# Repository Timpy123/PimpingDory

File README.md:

# PimpingDory

Two things live here:

1. **Software that talks to a [Chasing Dory](https://www.chasing.com) underwater
   drone without the vendor app** — download the media, watch the live camera,
   read telemetry, work the lights, drive the thrusters. No account, no login,
   no phone.
2. **A log of modifying the hardware** — a light rig, a bigger battery, more
   thrust, more storage, and a home-built metal detector. Some of it built, none
   of it finished, all of it written down.

Everything was worked out from the outside and tested on a real drone.
Not affiliated with or endorsed by Chasing.

## Hardware upgrades

Each one has its own folder with notes, photos and parts.

| upgrade | what | state |
|---|---|---|
| [**Light rig**](LightRig/) | two Wurkkos DL07 lights on an aluminium arm clamped to the hull | contour taken, aluminium strap trial-fitted |
| [**Metal detector**](MetalDetector/) | a self-contained pulse-induction pod that reports into the camera's view | plan, firmware and board done; nothing built |
| [**Battery**](BatteryUpgrade/) | recell the 1P3S 21700 pack | blocked on measuring peak current in water |
| [**Motors**](MotorUpgrade/) | more powerful thrusters | layout and drive understood, nothing ordered |
| [**Camera**](CameraUpgrade/) | higher resolution than the stock 1080p30 | not started |
| [**Storage**](StorageUpgrade/) | is the 16 GB an SD card, and can it be `dd`'d bigger | not started |

Further down: [what is inside the drone](#what-is-inside), [how to open
it](#opening-it), and [tools and parts](#tools-and-parts).

## The software

### Quick start

Join the drone's Wi-Fi — `Dory_xxxxx`, password `12345678` — then:

```sh
./scripts/DoryControl.sh --retrievemedia
```

Everything on the card lands in `./media`. On Windows the same options work
through `.\scripts\DoryControl.bat`.

```sh
./scripts/DoryControl.sh --list                       # what is on the card
./scripts/DoryControl.sh --api                        # what every endpoint answers
./scripts/DoryControl.sh --retrievemedia ~/dive       # download somewhere else
./scripts/DoryControl.sh --retrievemedia --removemedia # download, then free the card
./scripts/DoryControl.sh --video                      # live picture in VLC
./scripts/DoryControl.sh --video ./dive.mp4           # watch and record at once
./scripts/DoryControl.sh --telemetry                  # depth, battery, heading
./scripts/DoryControl.sh --lights on                  # headlights, or off, or 1-100
./scripts/DoryControl.sh --control --power 30         # drive it from the keyboard
```

`--help` lists every option.

To keep the link open between commands, run `--daemon` and talk to it. The
daemon starts itself if it is not already running:

```sh
./scripts/DoryControl.sh --send arm
./scripts/DoryControl.sh --send "forward 2"
./scripts/DoryControl.sh --send status
./scripts/DoryControl.sh --send quit
```

### What you need

- **Python 3** and **curl**. macOS, Linux and Windows 10+ all work; Windows
  does not ship Python, so install it first.
- **VLC** for `--video`. It is found automatically. Without it the script
  serves the stream to a browser instead, which needs **ffmpeg**; with neither
  it says so and names both rather than failing obscurely.
- On **macOS**, anything that listens on a UDP port wants `sudo` — see the
  firewall note below. Nothing else needs it.

### What works, and what does not

| | state |
|---|---|
| list, download, resume, verified delete | works |
| live video in VLC | works |
| telemetry — depth, battery, voltage, heading | works |
| headlights, 1–100 | works |
| arming and driving every thruster axis | works |
| recording to a file alongside the live view | records; a playable file has not been confirmed |
| **which thruster each axis drives** | derived from the firmware, [not yet watched in water](#the-axis-mapping) |
| the Windows launcher | written, [never run on Windows](#windows) |

### Things that will bite you

**Nothing is pushed at you until you ask.** The buoy relays no video and no
telemetry until a client completes a handshake on UDP 40000, and the vehicle
itself has every telemetry stream rate set to zero. Bind a socket and wait and
you get nothing at all, and it is not a fault. The script does the handshake
and asks for the streams automatically; `--no-netcode` skips the handshake, for
comparing against a client that does not do it.

**On macOS the firewall silently eats inbound UDP.** Not "blocks with an
error" — the packets never reach the process at all. A packet capture will show
thousands of them arriving on the wire while the socket bound to that exact
port reports silence. So every mode that listens lowers the firewall for the
session and puts it back on exit, which is why those modes want `sudo -v`
first. Downloading never touches it. On Windows, allow Python through the
firewall prompt when it appears.

**Filenames are never percent-encoded.** The buoy does not decode them, so
`20260717_133442(1).mp4` sent as `…%281%29.mp4` comes back `500`. Any
filename with brackets in it hits this.

**Expect dropouts.** The buoy's range is about 15 m. Downloads are checked
against the size the API reports and completed files are skipped, so re-running
after a dropout resumes rather than restarts.

**`--removemedia` never deletes a file it cannot prove you have.** With
`--retrievemedia` it downloads first, re-checks each file on disk against the
reported size, and only then issues the `DELETE`. Anything that failed to
download stays on the device. On its own it is deleting your only copy — add
`--confirm` and it demands a typed confirmation.

**`--debug` narrates every decision** — each request and reply, which host
answered, which response shape matched, the exact player command, the raw
telemetry before scaling. It goes to stderr, so `2>/dev/null` still leaves
clean output, and it all lands in `<path>/_run.txt` either way. That matters:
there is no internet on the buoy's Wi-Fi, so a bad trip has to be diagnosable
afterwards from the log alone.

### Driving it

`--control` takes the control role over REST, sends a 1 Hz heartbeat and RC
frames at 40 Hz, sets manual mode and arms. Arrow keys, `w`/`s`, `q`/`e`,
`r`/`f`; `a` to arm, space for neutral, `x` to quit. `--power N` sets how hard
it pushes.

**The vendor app has no failsafe at all** — on disconnect it stops sending and
that is that. This does the opposite: every key decays to neutral after 400 ms
unless repeated, and quitting sends twenty neutral frames followed by a disarm.

Try it in a bucket with the tether in hand before you try it over deep water.
The drone should not be run dry for long: the manual warns it can seize the
motors.

### Testing

`scripts/DoryTest.sh` exercises everything against the real drone and writes a
timestamped log meant to be read cold. Individual checks:

```sh
./scripts/DoryTest.sh --sweep      # drive every axis in turn, 8s each
./scripts/DoryTest.sh --identify   # what firmware, and every parameter
./scripts/DoryTest.sh --probe      # one arm, one movement, every byte logged
./scripts/DoryTest.sh --diagnose   # every theory at once, about 90s
```

The full suite, with no arguments, **ends by erasing the card**; `--keep`
skips the deletes.

### How it fits together

```
DoryControl.sh   ─┐
                  ├─→  scripts/dorycontrol.py    all the logic
DoryControl.bat  ─┘    (Windows goes via DoryControl.ps1)
```

The launchers do one job each: gather the network facts, export them, hand
over. One implementation, so the platforms cannot drift apart.

---

## What is inside

### It runs ArduSub

`--identify` pulls all **588 parameters** off the vehicle. The underwater-only
ones settle what it is — they exist in no other ArduPilot build:

```
FS_LEAK_ENABLE    FS_PRESS_ENABLE   FS_TEMP_ENABLE
SURFACE_DEPTH     GND_SPEC_GRAV     MOT_1..8_DIRECTION
```

alongside eight core ArduPilot families (`AHRS_ ATC_ BRD_ COMPASS_ EK2_ INS_
RC1_ SR0_`). It reports **flight sw 1.1.6**, which is Chasing's own numbering
rather than ArduPilot's 3.x/4.x, and uses **`FRAME`, not `FRAME_CONFIG`** — an
older ArduSub, before that parameter was renamed.

Values worth knowing:

| parameter | value | meaning |
|---|---|---|
| `ARMING_CHECK` | 0 | **pre-arm checks disabled** — which is why it arms with no GPS and no calibration |
| `FS_GCS_ENABLE` | 2 | GCS-loss failsafe **active**, hence `MYGCS: 255, heartbeat lost` if the heartbeat stops |
| `FS_LEAK_ENABLE` | 0 | leak failsafe off |
| `SURFACE_DEPTH` | -10 | 10 cm counts as the surface |
| `BATT_MONITOR` | 5 | analogue voltage and current |
| `FRAME` | 1 | VECTORED thruster layout |
| `MOT_1..8_DIRECTION` | ±1 | eight thruster channels, though the drone has five |

**Keep the parameter dump.** It is the only record of how a given vehicle is
configured, and there is no way to recover it.

### The flight controller

**The board cannot be identified from software.** `AUTOPILOT_VERSION` returns
board, vendor and product ids all zero, and `BRD_SERIAL_NUM` is 0 too. Only
opening it would answer that.

What the parameters do establish:

- **Pixhawk-class hardware.** The `BRD_*` set — `BRD_PWM_COUNT`,
  `BRD_SER1_RTSCTS`, `BRD_SAFETYENABLE`, `BRD_CAN_ENABLE` — is the PX4/Pixhawk
  HAL, so that family or a clone of it, not an APM or a bespoke stack.
- **Six PWM outputs.** `BRD_PWM_COUNT = 6`, and of the aux channels only
  `RC6_FUNCTION = 56` is set, which is RCIN6 pass-through. So outputs **1–5 are
  the thrusters and output 6 is the light**, straight from RC channel 6.
- **Compass**: `COMPASS_DEV_ID = 68873` decodes to I²C bus 1, address `0x0D` —
  an HMC5883/QMC5883-class magnetometer, the commodity part.

### The ESCs

Nothing, and that is expected rather than a gap. `RC_SPEED = 490` is plain PWM
at 490 Hz; there is no `MOT_PWM_TYPE`, no `ESC_*` parameters and no ESC
telemetry. They are dumb output stages that take a pulse width and report
nothing back, so no protocol exists by which the firmware could know what they
are. No DShot or OneShot either — anything expecting RPM feedback or per-motor
current has nothing to talk to.

### The thrusters

The compute module's plug layout names every one:

| plug | goes to |
|---|---|
| **1** | Motor — Left Vertical Thruster |
| **2** | Motor — Left Thruster |
| **3** | Motor — Rear Vertical Thruster |
| **4** | Motor — Right Thruster |
| **5** | Motor — Right Vertical Thruster |
| **6** | Breathing Light |
| **7** | Connector — twisted-pair cable |
| **8** | Connector — three-colour cable |
| **9** | LED Lights |

> **Note:** always check if O-rings are damaged and need replacing.

**Two horizontal and three vertical, and no lateral thruster** — the drone
cannot strafe sideways. That is why RC channel 5 was free for Chasing to
repurpose as the lights: in stock ArduSub channel 5 is *lateral*, and this hull
has nothing to connect it to.

### The axis mapping

ArduSub's channel-to-axis mapping is fixed in the firmware, not configurable,
so knowing it is ArduSub gives the mapping:

| slot | axis | typed command | key | how the thrusters produce it |
|---|---|---|---|---|
| 4 | **forward / back** | `forward` `back` | ↑ ↓ | both horizontals together |
| 2 | **vertical** | `up` `down` | `w` `s` | all three verticals together |
| 3 | **yaw** | `left` `right` | ← → | the horizontals, differentially |
| 0 | roll | `rollleft` `rollright` | `q` `e` | left vertical against right |
| 1 | pitch | `pitchup` `pitchdown` | `r` `f` | the front verticals against the rear |
| 5 | *lateral* in stock ArduSub | — | — | **nothing — repurposed as the lights** |

Typed commands are named for what they do, so `--send "up 2"` ascends. The
arrow keys follow the joystick convention instead — pushing a stick away from
you is forwards — which is why ↑ is forward but `w` is up. Pitch is inverted
on the wire.

**Not yet confirmed in water.** The control path works — it arms and every
input drives — but which thruster each slot actually turns can only be seen,
not logged.
`./scripts/DoryTest.sh --sweep` runs each in turn and announces it; in a
bucket, with the tether in hand.

### Dead ends, recorded so nobody retries them

- **The app** needs account registration, and login needs an internet
  connection the buoy's Wi-Fi does not have.
- **SSH.** Port 22 is open on the ROV but the daemon is ancient and modern
  OpenSSH refuses to negotiate. It connects with `-o
  KexAlgorithms=+diffie-hellman-group1-sha1 -o HostKeyAlgorithms=+ssh-rsa -o
  Ciphers=+aes128-cbc`, but the root password is unknown. Unnecessary anyway.
- `nmap` finds only 22 and 80 open.
- The manual documents **no** USB or computer transfer. App-only, officially.

### Reflashing it

**Unknown, untried, and not to be attempted without a recovery path.** An
underwater drone with no way back is a brick, and the vendor app is the only
official route.

What is known: it answers `AUTOPILOT_VERSION` but identifies no board, and
all 588 parameters are readable and say ArduSub. What is not: where the
firmware physically lives — the flight controller is a separate MCU behind the
buoy's Linux box, so any reflash is likely *through* it — and whether a stock
build even targets this board. "Pixhawk-family" is not a build target, and the
thruster mapping and the light on output 6 are Chasing's own and would be
lost.

---

## The hardware itself

| | |
|---|---|
| **Drone** | 247 × 188 × 92 mm, 1.1 kg. Camera, 5 thrusters, 15 m max depth, ~60 min runtime. Tethered to the buoy; no Wi-Fi of its own |
| **Buoy** | 130 × 130 × 88 mm, 160 g. Floats, relays Wi-Fi, and **holds the 16 GB of media** — it is the thing to talk to |
| **Media** | JPEG 1920×1080 stills, MP4 H.264 1080p30 video |

### Opening it

The cover is held by **ST2.2 × 6.5** self-tapping screws — DIN 7983 TX, A4
stainless — so replacements are available off the shelf.

There is also **one Torx security screw**, needing a **T6H** bit (the
pin-in-Torx variant) **on a 50 mm shaft**. The shaft length is the part that
catches people out: a stubby bit will not reach it.

[This video](https://www.youtube.com/watch?v=_ONTOr11_d4) covers most of the
part replacements.

### The connector nuts

The thruster and light leads use small circular IP68 connectors, the kind
usually described as "Ray Wu style" after the AliExpress seller — though the
keyway on these is not the same, so they are something else in the same family.

**If you recognise them, please open an issue.** The closest match by size is
the SP13/M13 family, but the keyway does not line up, and no supplier found so
far names the part. Knowing the manufacturer would make the plugs sourceable
instead of scavengeable.

**The nut is 13.5 mm and the socket that fits it is 14 mm**, which is half a
millimetre of slop. Wrap a little aluminium foil or paper round the nut before
putting the socket on: without it the socket will round the flats off, and a
rounded nut on a waterproof connector is not a small problem.

### Tools and parts

| what | for | where |
|---|---|---|
| **T6H bit set, 50 mm shaft** | the security screw — the long shaft is the point | [amazon.nl B0GXNLXH3R](https://www.amazon.nl/-/en/gp/product/B0GXNLXH3R/ref=ewc_pr_img_1) |
| **T6H screwdriver set** | the cover screws | [amazon.nl B0CZDN9Q1R](https://www.amazon.nl/dp/B0CZDN9Q1R?ref=ppx_yo2ov_dt_b_fed_asin_title) |
| **Lambda probe socket, 3/8" drive, 14 mm** (SW14, CrV, SL-2508-026) | undoing the IP68 connector nuts on the compute module. A lambda socket is slotted down one side so a cable can pass through it — which is exactly what a nut with a cable coming out of it needs. The nut is 13.5 mm, so pack it out with a wrap of paper or aluminium foil before turning it, or the socket will round the flats off | [amazon.nl B0FMR3Q7K2](https://www.amazon.nl/dp/B0FMR3Q7K2) |
| **ST2.2 × 6.5 screws**, DIN 7983 TX, A4 | replacing the cover screws | [rvspaleis.nl](https://www.rvspaleis.nl/plaatschroeven/din-7983-tx/din-7983tx-[-]-a4-[-]-2,2/7983-4-2.2x6.5tx_1) |
| **Flat aluminium profile**, 20 × 2 × 2000 mm | the light-rig arm | [gamma.nl B175328](https://www.gamma.nl/assortiment/profiel-plat-aluminium-brut-20x2x2000mm/p/B175328) |
| **1/4 inch thread adapters** | mounting the lights to the arm — standard 1/4"-20 tripod thread | [amazon.nl B0DCGCCXQC](https://www.amazon.nl/dp/B0DCGCCXQC?ref=ppx_yo2ov_dt_b_fed_asin_title) |
| **1/4"-20 nuts and washers**, 150 pc, 304 stainless | fastening the thread through a bottom and a top bar | [amazon.nl B0B1DZPQ1R](https://www.amazon.nl/-/en/dp/B0B1DZPQ1R) |
| **Wurkkos DL07 diving flashlight** ×2, 1 × 26650 each | the light rig | [wurkkos.com](https://wurkkos.com/products/wurkkos-dl07-diving-flashlight?VariantsId=12525) |

### 3D printed parts

| what | for | where |
|---|---|---|
| **Wifi Buoy Tether Loop** by rsoko | securing the buoy with a tether — clips on for a leash | [thingiverse thing:4031565](https://www.thingiverse.com/thing:4031565/files) |

---

## Still open

- **The axis mapping**, in water — see [above](#the-axis-mapping). One sweep in
  a bucket settles it.
- **Peak current under load.** The pack is 1P, so one cell carries everything,
  and that decides which 21700 can replace it. It has to be measured wet: in
  air a propeller with nothing to push draws almost nothing.
  See [`BatteryUpgrade/`](BatteryUpgrade/).
- **Windows.** `DoryControl.bat` → `DoryControl.ps1` →
  `dorycontrol.py`. The Python half is the code that works elsewhere, so the
  risk is concentrated in the launcher: the network facts and the argument
  parsing. `scripts/WINDOWS-NOTES.md` lists what is most likely wrong.

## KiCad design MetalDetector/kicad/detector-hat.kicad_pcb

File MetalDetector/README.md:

# Metal detector pod

A **self-contained pulse-induction metal detector** for the Chasing Dory.
Its own battery, no data connection to the drone at all — it reports by being
*visible to the drone's camera*: an LED strip and a small OLED sitting in the
bottom edge of the frame.

Target: a coin-sized non-ferrous object at **15–30 cm**, against about **4 cm**
for Chasing's own detector, which is ferrous-only and sold only inside a
€480–600 bundle.

## Why it reports optically

There is no channel to report on. The Dory's compute module has ten plugs and
every one is taken: 1–5 the thrusters, 6 the breathing light, 9 the LED lights,
7–8 the tether pair. Nothing spare, and adding a conductor means opening a
pressure housing.

So the pod says nothing electrically and everything visually — the same channel
Chasing's stock detector uses, and it works because you are already watching
the camera.

## Why pulse induction

PI is the standard for underwater and beach detectors: largely indifferent to
water, salt and bottom mineralisation, where a VLF detector needs constant
ground balancing. One coil does both transmit and receive. It finds every
conductive metal with no discrimination — fine when the plan is "go look with
the camera".

The MCU switches 1–2 A through the coil for ~150 µs, cuts it, and measures how
slowly the field decays. Metal nearby decays slower. Repeat 100×/s, track the
baseline, report the deviation.

## What is here

```
PLAN-DETECTOR-POD.md     the build plan — the authoritative document
docs/HAT-SCHEMATIC-SPEC.md   the circuit
kicad/                   the HAT board: schematic, PCB, fab outputs
src/detector-firmware/   the firmware (C, pico-sdk)

toolchain.sh             fetch the ARM cross-compiler   (976 MB)
sdk.sh                   fetch the Pico SDK             (37 MB)
freerouting.sh           fetch the autorouter           (137 MB)
build.sh                 build the firmware
```

The four scripts sit at the root, not in `src/`, because `src/` is *what they
fetch* — a `rm -rf src` to start clean must not delete the tools that rebuild
it.

## Building the firmware

```sh
./toolchain.sh
./sdk.sh
./build.sh
```

macOS and Linux, Intel and ARM. Each script detects the host and picks the
right download; `build.sh` checks that everything it needs is present and names
what is missing rather than failing part-way through.

Output is `src/detector-firmware/build/detector-firmware.uf2`. To flash it,
hold BOOTSEL while plugging the Pico in and copy the `.uf2` onto the `RPI-RP2`
drive that appears. Debug console is 115200 baud on UART0 (GP0 = TX).

```sh
./build.sh --clean     throw the build directory away first
./build.sh --debug     build with debug symbols
```

**Nothing is downloaded twice.** Each script finds an existing install and asks
before replacing it; non-interactively it keeps what is there and tells you to
pass `--force`.

**None of the fetched content is in git** — 1.3 GB of vendor binaries and
upstream checkouts, all reproducible from these scripts, and two of them carry
their own `.git` directories. Pinned versions: ARM 14.2.rel1, pico-sdk 2.3.0,
Freerouting 2.2.4.

`picotool` has no script: cmake fetches it itself on the first configure.

## The board

One JLCPCB-assembled carrier for a Raspberry Pi Pico, holding the pulse
generator, the receive chain, power, and the connectors for coil, display,
strip, sounder and depth sensor. `kicad/fab/` has the gerbers, BOM and
pick-and-place files with ordering notes.

**The board is generated, not drawn.** `sch_gen.py` emits the schematic from
component tables and `pcb_gen.py` emits the PCB from a placement table, so the
source of truth is those scripts rather than the `.kicad_*` files. Moves made
by hand in the GUI are pulled back into the table with `sync_place.py` — do
that before any regeneration, or they are lost.

### The pipeline

`kicad/tools/go.sh` runs the whole thing in one shot: regenerate → flip the
bottom-side parts and rip all tracks → Freerouting → import the result and fill
zones → report stranded copper → stitch islands → silk → sync → signal check.

**It is destructive by design** — stage 2 removes every track on the board
before rerouting. Fine when that is what you want; not something to run
casually.

### Every tool in `kicad/tools/`

| tool | what it does |
|---|---|
| **`go.sh`** | the whole reroute pipeline, 8 stages. **Rips all tracks first** |
| `sch_gen.py` | emit the schematic from the component/label tables |
| `pcb_gen.py` | emit the PCB from the `PLACE` floorplan table |
| `sync_place.py` | pull GUI moves back into `pcb_gen.py`'s table so they survive a regen |
| `route.py` | grid A* autorouter, routes every net including GND |
| `route_remainder.py` | grid A*/Dijkstra for the few nets Freerouting cannot close, against the real board |
| `check_unrouted.py` | name the genuinely unrouted nets — DRC's own list is noisy with GND zone fragments |
| `signal_check.py` | list genuinely-open signal connections from a `kicad-cli` DRC report |
| `stitch_islands.py` | join isolated GND pour islands with the fewest vias, only where an island exists |
| `silk.py` | pin-1 dots, battery polarity, board name. Re-run after any regen — it wipes them |
| `heat_check.py` | flag heat sources sitting too close to heat-sensitive parts, including stacked through the FR4 |
| `orient_search.py` | try rotations and flips of chosen parts, route each, keep the best |
| `pinmap_trial.py` | try connector pin assignments and route each to compare |
| `fab_gen.sh` | build the JLCPCB package: gerbers zip, BOM, pick-and-place |
| `make_jlc_csv.py` | reshape `kicad-cli`'s raw exports into JLCPCB's column names |
| `backup.sh` | timestamped tarball of `kicad/` into `../tmp/backups` |
| `kicad_paths.sh` | find KiCad and Freerouting on this machine. Sourced by the shell tools, never run |
| `kicad_paths.py` | the same, imported by the Python tools |

Most take KiCad's own Python, and are run **from `kicad/`**, not from
`tools/` — for example `tools/go.sh` or `python3 tools/pcb_gen.py`.

### Paths, and other machines

The tools used to hardcode `/Applications/KiCad/KiCad.app/...`, correct on one
Mac and wrong everywhere else. They now resolve through `kicad_paths.sh` and
`kicad_paths.py`, which look in the usual macOS and Linux locations and fail
with something actionable if a piece is missing. Override any of them in the
environment:

```sh
KICAD_CLI=/path/to/kicad-cli KICAD_PY=/path/to/python3 tools/go.sh
```

| variable | what it points at | Linux |
|---|---|---|
| `KICAD_CLI` | `kicad-cli`, for gerber/drill/DRC export | `apt install kicad` |
| `KICAD_PY` | a python that can `import pcbnew` | `apt install kicad python3-pcbnew` |
| `KICAD_FP` | KiCad's stock footprint libraries | `/usr/share/kicad/footprints` |
| `FR` | Freerouting | `./freerouting.sh` |

**Untested on Linux.** The path resolution is written for it and the pipeline
itself is platform-neutral, but nobody has run it there.

## Status

Plan written, firmware written, board laid out. **Nothing has been built or
tested in water.** The test protocol is §7 of the plan; the interference test
against running thrusters is the one that decides whether this works on this
drone at all.

## Open questions worth answering early

- **The drone has a magnetometer.** It runs ArduSub with a compass on I²C and
  reports heading in telemetry. A coil pulsing 1–2 A a few centimetres away is
  a large alternating field next to it, and nothing compensates for that.
  Heading may be unusable while the detector runs. Measurable now: run
  `../scripts/DoryControl.sh --telemetry` and watch `hdg` with the coil
  pulsing.
- **Size.** The Dory is 247 × 188 × 92 mm, 1.1 kg, five thrusters, and **no
  lateral thruster** — it cannot crab sideways to hold station. A 50 mm pod
  plus a 20 cm coil ring below it is a lot of drag on a small platform. A
  cardboard-and-lead mockup of the final envelope, flown before any epoxy is
  mixed, answers this cheaply.
- **Thrusters must not be run dry.** The manual is explicit that it can seize
  the motors, so the interference test has to happen in water.

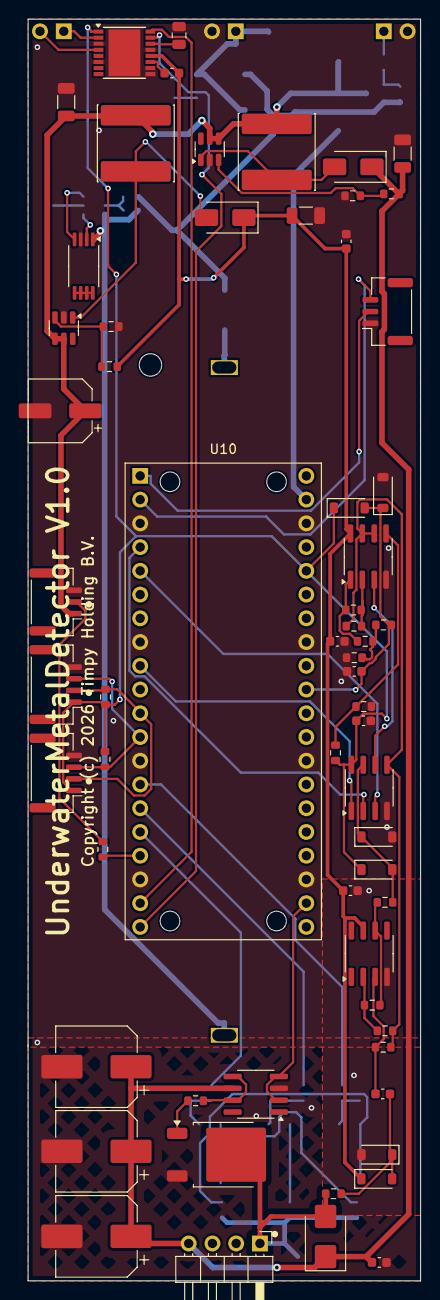
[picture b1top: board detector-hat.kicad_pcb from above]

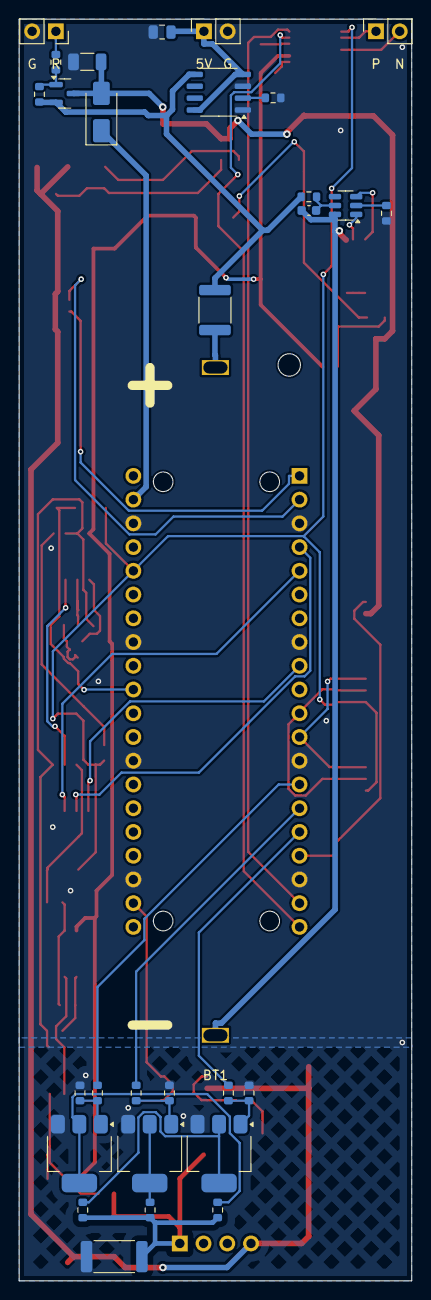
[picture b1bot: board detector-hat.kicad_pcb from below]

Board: 2 copper layers, 42.0 x 135.0 mm, 92 parts (30 on the bottom side), 62 nets.

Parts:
BT1: BatteryHolder_MYOUNG_A6AJ002
C1, C18: C_0805_2012Metric
C2, C10, C11, C12, C13, C14, C16, C17, C19: C_0603_1608Metric
C3, C4, C5, C6: C_1206_3216Metric
C7, C8, C9: CP_Elec_8x10.5
C20: CP_Elec_6.3x7.7
D1, D7, D8: D_SMA
D2: D_SMB
D3, D4, D5, D6, D9, D10: D_SOD-123
F1: Fuse_1812_4532Metric
J1, J2, J3: PinSocket_1x02_P2.54mm_Vertical
J4: PinHeader_1x04_P2.54mm_Horizontal
J6, J7: JST_GH_BM04B-GHS-TBT_1x04-1MP_P1.25mm_Vertical
J8: JST_GH_BM03B-GHS-TBT_1x03-1MP_P1.25mm_Vertical
J9: JST_GH_SM03B-GHS-TB_1x03-1MP_P1.25mm_Horizontal
L1, L2: L_Sunlord_SWPA8040S
Q1: SOT-23
Q2: TSSOP-8_4.4x3mm_P0.65mm
Q3: TO-252-2
Q4, Q5, Q6: SOT-223
R1, R2, R5, R6, R7, R8, R9, R11, R12, R13, R14, R15, R16, R17, R18, R20, R21, R22, R23, R24, R25, R26, R30, R31, R32, R40, R41, R42, R43, R44, R45, R47, R48, R49: R_0603_1608Metric
R10: R_2512_6332Metric
U1: SO-8_3.9x4.9mm_P1.27mm
U2, U3, U4: SOT-23-6
U5, U6, U7, U9: SOIC-8_3.9x4.9mm_P1.27mm
U8: HTSSOP-16-1EP_4.4x5mm_P0.65mm_EP3.4x5mm
U10: RPi_Pico_Socket

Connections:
3V3: C16.1, D5.1, D9.1, J6.1, J7.1, R31.1, R32.1, R42.1, U7.8, U8.1, U10.36
BAT_NEG: BT1.2, C2.2, Q2.1, U2.6
COIL_A: D2.2, J4.1, Q3.2, R10.1, R11.1, R12.1, R13.1, R20.1
DAMP0: R16.1, U10.14
DAMP1: R17.1, U10.15
DAMP2: R18.1, U10.16
DG0: Q4.1, R16.2, R24.1
DG1: Q5.1, R17.2, R25.1
DG2: Q6.1, R18.2, R26.1
DMP0: Q4.2, Q4.4, R11.2
DMP1: Q5.2, Q5.4, R12.2
DMP2: Q6.2, Q6.4, R13.2
DRV_OUT: R23.1, U5.5, U5.7
DRV_VCP: C17.1, U8.11
DRV_VINT: C18.1, U8.14
DW_CS: R6.1, U2.2
DW_OC: Q2.4, U2.3
DW_OD: Q2.2, U2.1
DW_VCC: C2.1, R5.2, U2.5
FB1: R8.2, R9.1, U3.3
FB2: R14.2, R15.1, U4.3
FET_D: Q2.5, Q2.6, Q2.7, Q2.8
GND: C1.2, C3.2, C4.2, C5.2, C6.2, C7.2, C8.2, C9.2, C10.2, C12.2, C13.2, C14.2, C16.2, C18.2, C19.2, C20.2, D4.2, D6.2, D10.2, J2.2, J3.2, J6.4, J7.4, J8.3, J9.1, Q2.3, Q3.3, Q4.3, Q5.3, Q6.3, R6.2, R7.2, R9.2, R10.2, R15.2, R22.2, R24.2, R25.2, R26.2, R43.2, U1.1, U1.3, U3.2, U4.2, U5.3, U6.4, U7.4, U8.3, U8.6, U8.9, U8.10, U8.13, U8.17, U9.4, U10.3, U10.8, U10.13, U10.18, U10.23, U10.28, U10.33, U10.38
I2C_SCL: J6.3, J7.3, R32.2, U10.12
I2C_SDA: J6.2, J7.2, R31.2, U10.11
PIEZO_N: J1.2, U8.4
PIEZO_P: J1.1, U8.2
POT_A: D9.2, D10.1, R48.2, U7.7
POT_CS: U7.1, U10.9
Q1_G: Q1.1, R1.2, R2.1
Q3_G: Q3.1, R23.2
REED: J2.1, R2.2
RX_ADC: C13.1, D5.2, D6.1, R47.2, U10.31
RX_B: C11.2, R49.1, U6.3
RX_CL: C11.1, D3.2, D4.1, R20.2
RX_DIV: R21.2, R22.1, R47.1
SND_A: U8.16, U10.19
SND_B: U8.15, U10.20
SPI_MOSI: U7.3, U10.5
SPI_SCK: U7.2, U10.4
STG2_IN: U7.6, U9.3
STG2_OUT: R21.1, R44.1, U9.1
SW1: D1.2, L1.2, U3.1
SW2: D8.2, L2.2, U4.1
TP_PROG: R7.1, U1.2
TX_GATE: U5.2, U5.4, U10.22
U6_FB: R40.1, R41.2, U6.2
U6_OUT: R41.1, R48.1, U6.6
U9_FB: R44.2, R45.1, U9.2
UART_RX: J9.3, U10.2
UART_TX: J9.2, U10.1
V9_SND: C6.1, C12.1, C14.1, C17.2, C19.1, D3.1, D8.1, R14.1, U6.7, U8.12, U9.8
V12_TX: C4.1, C7.1, C8.1, C9.1, C10.1, D1.1, D2.1, J4.4, R8.1, U5.6
VBAT_P: F1.2, Q1.2, R1.1, R5.1, U1.5
VBAT_RAW: BT1.1, F1.1
VBAT_SW: C3.1, C5.1, C20.1, D7.2, J8.1, L1.1, L2.1, Q1.3, U3.4, U3.5, U4.4, U4.5
VBUS_C: C1.1, J3.1, U1.4, U1.8
VREF: R40.2, R45.2, R49.2, U7.5, U9.6, U9.7
VREF_DIV: R42.2, R43.1, U9.5
VSYS_PICO: D7.1, U10.39
WS_DATA: J8.2, R30.2
WS_GP: R30.1, U10.17

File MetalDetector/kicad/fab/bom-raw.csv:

"Reference","Value","Footprint","LCSC"
"BT1","18650 THT terminals mid-board bottom (MYOUNG BH-18650-A6AJ002)","hat:BatteryHolder_MYOUNG_A6AJ002","C19184085"
"C1","10uF 25V","Capacitor_SMD:C_0805_2012Metric","C440198"
"C2,C10,C11,C12,C14,C16,C19","100nF 50V","Capacitor_SMD:C_0603_1608Metric","C14663"
"C3,C4,C5,C6","22uF 25V","Capacitor_SMD:C_1206_3216Metric","C12891"
"C7,C8,C9","220uF 25V","Capacitor_SMD:CP_Elec_8x10.5","C4747974"
"C13","220pF 50V","Capacitor_SMD:C_0603_1608Metric","C1603"
"C17","10nF 25V","Capacitor_SMD:C_0603_1608Metric","C57112"
"C18","2.2uF 16V","Capacitor_SMD:C_0805_2012Metric","C377773"
"C20","100uF 10V","Capacitor_SMD:CP_Elec_6.3x7.7","C2891567"
"D1,D7,D8","SS34","Diode_SMD:D_SMA","C8678"
"D2","MUR160","Diode_SMD:D_SMB","C2940198"
"D3,D4","1N4148W","Diode_SMD:D_SOD-123","C81598"
"D5,D6,D9,D10","BAT54W","Diode_SMD:D_SOD-123","C7502705"
"F1","polyfuse 2A","Fuse:Fuse_1812_4532Metric","C3102"
"J1","piezo dock (1x2 socket)","Connector_PinSocket_2.54mm:PinSocket_1x02_P2.54mm_Vertical",""
"J2","power switch dock (1x2 socket)","Connector_PinSocket_2.54mm:PinSocket_1x02_P2.54mm_Vertical",""
"J3","5V charge input (1x2 socket, ext micro-USB)","Connector_PinSocket_2.54mm:PinSocket_1x02_P2.54mm_Vertical",""
"J4","coil dock: 1x4 right-angle header, outer pins only (7.62mm gap for 300V)","Connector_PinHeader_2.54mm:PinHeader_1x04_P2.54mm_Horizontal","C32713263"
"J6","OLED I2C dock (GH BM04B-GHS-TBT)","Connector_JST:JST_GH_BM04B-GHS-TBT_1x04-1MP_P1.25mm_Vertical",""
"J7","depth meter I2C dock (GH BM04B-GHS-TBT)","Connector_JST:JST_GH_BM04B-GHS-TBT_1x04-1MP_P1.25mm_Vertical",""
"J8","WS2812 LED dock (GH BM03B-GHS-TBT)","Connector_JST:JST_GH_BM03B-GHS-TBT_1x03-1MP_P1.25mm_Vertical",""
"J9","debug UART (GH)","Connector_JST:JST_GH_SM03B-GHS-TB_1x03-1MP_P1.25mm_Horizontal","C54582898"
"L1,L2","22uH 3A","Inductor_SMD:L_Sunlord_SWPA8040S","C15857"
"Q1","AO3401A","Package_TO_SOT_SMD:SOT-23","C15127"
"Q2","FS8205A","Package_SO:TSSOP-8_4.4x3mm_P0.65mm","C5148694"
"Q3","STF10N60","Package_TO_SOT_SMD:TO-252-2","C2764050"
"Q4,Q5,Q6","STN1HNK60","Package_TO_SOT_SMD:SOT-223","C39303"
"R1,R24,R25,R26,R49","100k","Resistor_SMD:R_0603_1608Metric","C25803"
"R2,R6,R20,R45,R47,R48","1k","Resistor_SMD:R_0603_1608Metric","C22548"
"R5,R16,R17,R18,R40","100R","Resistor_SMD:R_0603_1608Metric","C22775"
"R7","1k2","Resistor_SMD:R_0603_1608Metric","C22765"
"R8","191k","Resistor_SMD:R_0603_1608Metric","C22932"
"R9,R15,R41,R42,R43","10k","Resistor_SMD:R_0603_1608Metric","C98220"
"R10","1k 2W","Resistor_SMD:R_2512_6332Metric","C175457"
"R11","680R","Resistor_SMD:R_0603_1608Metric","C23228"
"R12,R30","330R","Resistor_SMD:R_0603_1608Metric","C23138"
"R13","150R","Resistor_SMD:R_0603_1608Metric","C22808"
"R14","140k","Resistor_SMD:R_0603_1608Metric","C185372"
"R21","6k8","Resistor_SMD:R_0603_1608Metric","C23212"
"R22","3k3","Resistor_SMD:R_0603_1608Metric","C22978"
"R23","10R","Resistor_SMD:R_0603_1608Metric","C22859"
"R31,R32","4k7","Resistor_SMD:R_0603_1608Metric","C23162"
"R44","9k1","Resistor_SMD:R_0603_1608Metric","C23260"
"U1","TP4056","Package_SO:SO-8_3.9x4.9mm_P1.27mm","C382139"
"U2","DW01A","Package_TO_SOT_SMD:SOT-23-6","C18164398"
"U3","MT3608 12V","Package_TO_SOT_SMD:SOT-23-6","C19189893"
"U4","MT3608 9V","Package_TO_SOT_SMD:SOT-23-6","C19189893"
"U5","TC4427","Package_SO:SOIC-8_3.9x4.9mm_P1.27mm","C20551"
"U6","NE5534","Package_SO:SOIC-8_3.9x4.9mm_P1.27mm","C49396707"
"U7","MCP41010","Package_SO:SOIC-8_3.9x4.9mm_P1.27mm","C136395"
"U8","DRV8833PWP","Package_SO:HTSSOP-16-1EP_4.4x5mm_P0.65mm_EP3.4x5mm","C50506"
"U9","TL072","Package_SO:SOIC-8_3.9x4.9mm_P1.27mm","C5157710"
"U10","Raspberry Pi Pico (socketed)","hat:RPi_Pico_Socket",""

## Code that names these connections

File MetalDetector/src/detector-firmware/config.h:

// Detector pod firmware v3 — pin map and tuning constants.
// Spec: PLAN-DETECTOR-POD.md "v3 specification"; hardware: docs/HAT-SCHEMATIC-SPEC.md.
// The pin map MUST match the HAT spec's Pico pin table.

#ifndef CONFIG_H
#define CONFIG_H

// ---- Pins (HAT v3) --------------------------------------------------------

// PI front end
#define PIN_TX_GATE             17  // coil pulse via TC4427 gate driver
#define PIN_RX_ADC              26  // decay signal, conditioned to 0-3.3V by RX chain
#define RX_ADC_INPUT            0
#define PIN_DAMP0               10  // damping bank select (binary, 3 bits)
#define PIN_DAMP1               11
#define PIN_DAMP2               12

// Digipot (RX gain), MCP41010 on SPI0
#define SPI_BUS                 spi0
#define PIN_SPI_SCK             2
#define PIN_SPI_MOSI            3
#define PIN_POT_CS              6

// DRV8833 (on-HAT) driving the potted piezo disc, push-pull.
// GP14/GP15 share one PWM slice (channels A/B) -> complementary output.
#define PIN_SOUNDER_A           14
#define PIN_SOUNDER_B           15

// WS2812 strip, single data line.
#define PIN_WS2812              13
#define WS2812_NUM_PIXELS       8

// I2C bus: OLED (and the LCD1602 on the bench). J7 is a free I2C port.
// v3: moved to GP8/GP9 (GP2-6 belong to the digipot SPI block on the HAT).
#define I2C_BUS                 i2c0
#define PIN_I2C_SDA             8
#define PIN_I2C_SCL             9
#define I2C_BAUD_HZ             400000
#define OLED_I2C_ADDR           0x3C

#define PIN_STATUS_LED          25  // onboard LED, mirrors heartbeat

// ---- PI engine (bench-calibrate on first hardware) -------------------------

#define TX_PULSE_US             150     // coil on-time per pulse
#define PULSE_PERIOD_MS         10      // 100 pulses/s
#define SAMPLE_START_US         15      // first ADC sample after switch-off (autotune refines)
#define DECAY_SAMPLES           64      // ADC free-run burst per pulse (~2us/sample)
#define EARLY_WINDOW            16      // samples 0..15: strength integral
#define LATE_WINDOW_END         48      // samples 16..47: tau (late/early ratio)
#define RING_THRESHOLD          40      // ADC counts: ringing detection in autotune
#define GAIN_TARGET_NOISE       6.0f    // autotune digipot: target noise std in counts
#define TAU_FAST_MAX            0.10f   // late/early below this -> class F (thin/small)
#define TAU_SLOW_MIN            0.30f   // above this -> class S (large/conductive); between -> M

// ---- Signal processing -----------------------------------------------------

#define LEVEL_EMA_MS            50      // fast smoothing of the per-pulse integral
#define CALIBRATION_MS          2000    // startup auto-zero duration
#define BASELINE_TAU_MS         60000   // slow drift tracking (targets fade in ~minutes)
#define DETECT_SIGMA            3.0f    // detection gate: signal > max(3*sigma, floor)
#define DETECT_FLOOR            2.0f    // minimum gate in integral counts
#define FULL_SCALE_SIGNAL       400.0f  // integral counts that map to strength 255 (bench-tune)

// ---- Sounder ---------------------------------------------------------------

#define SOUNDER_ENABLED         1       // compile-time mute
#define TONE_BASE_HZ            3000    // rises with strength up to ~4 kHz
#define TICK_MS                 30      // length of one beep tick
#define TICK_PERIOD_MAX_MS      800     // cadence at barely-detected
#define TICK_PERIOD_MIN_MS      80      // cadence just below continuous
#define CONTINUOUS_THRESHOLD    240     // strength >= this -> solid tone

// ---- Depth / temperature ----------------------------------------------------


// ---- Strip behavior ----------------------------------------------------------

#define STRIP_BRIGHTNESS        60      // 0-255 cap (potted LEDs are bright)
#define INSPECT_STABLE_MS       2000    // stable strong signal -> inspect mode
#define INSPECT_MIN_STRENGTH    40      // below this, never enter inspect mode
#define INSPECT_STABLE_BAND     26      // strength units (~10% of 255)
#define INSPECT_DIM_NUM         1       // dim to 1/10 in inspect mode
#define INSPECT_DIM_DEN         10

// ---- OLED layout (frozen v2 layout carried over; scales = calibration knob) --

#define OLED_W                  128
#define OLED_H                  32
#define LAYOUT_LEFT_W           80  // cols 0-79 text zone
#define LAYOUT_RIGHT_X          84  // cols 84-127 detection zone
#define TAU_ROW_Y               17  // tau icon row (was the temp line)
#define BAR_H                   14  // strength bar height, rows 0-13
#define DISPLAY_REFRESH_MS      200 // OLED redraw period (~12 ms I2C per flush)

// ---- Heartbeat / debug --------------------------------------------------------

#define HEARTBEAT_PERIOD_MS     2000    // "alive" blip interval (strip px 0, OLED dot, GP25)
#define HEARTBEAT_ON_MS         100
#define DEBUG_PRINT_PERIOD_MS   500     // level/baseline/strength/tau/depth/temp over UART (GP0)

#endif // CONFIG_H

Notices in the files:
MetalDetector/kicad/detector-hat.kicad_pcb:
Copyright (c) 2026 Timpy Holding B.V.
